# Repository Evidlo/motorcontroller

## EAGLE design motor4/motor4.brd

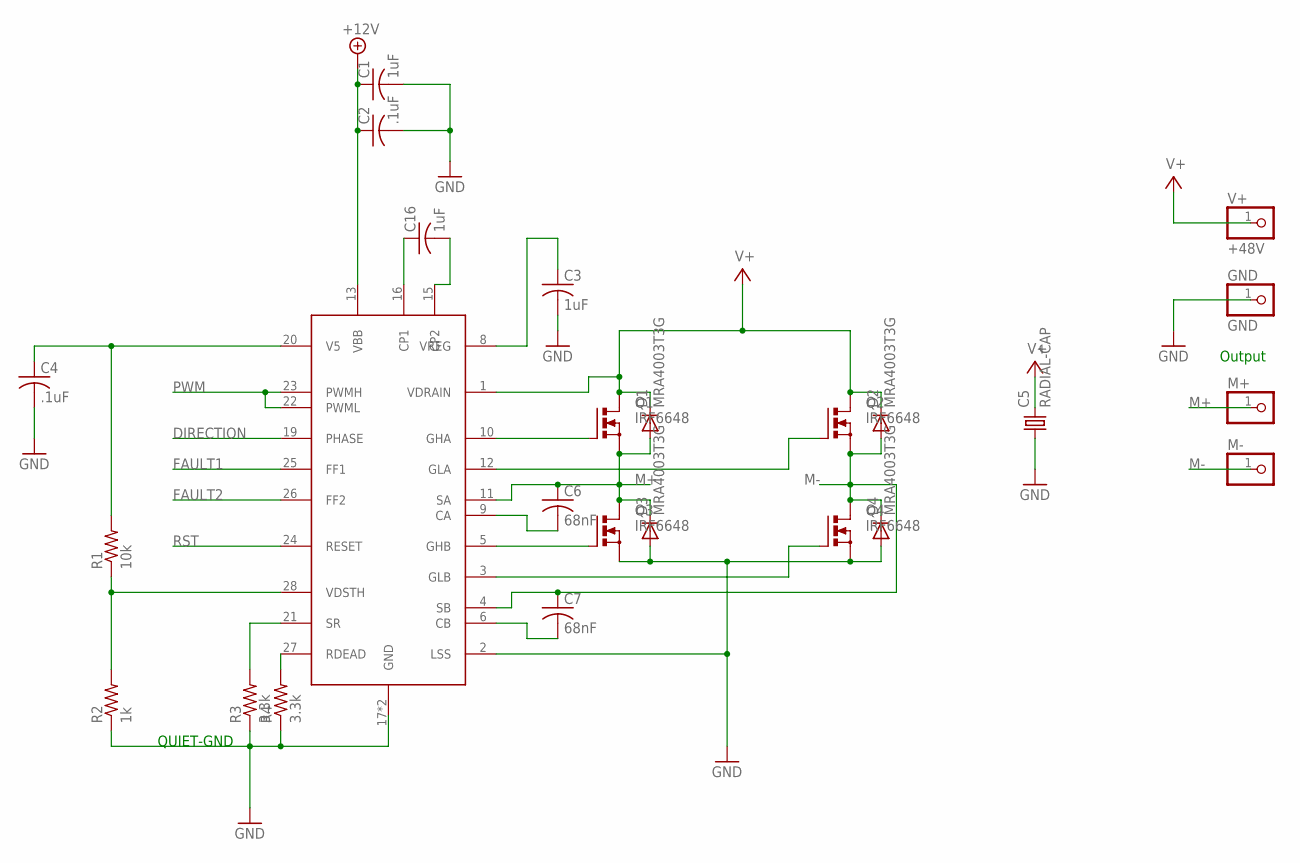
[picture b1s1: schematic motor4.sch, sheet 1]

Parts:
ALLGR: ALLEGRO-A3921; TSSOP28
C1, C3, C16: 1uF; C0603
C2, C4: .1uF; C0603
C5: RADIAL-CAP
C6, C7: 68nF; C0603
D1, D2, D3, D4: MRA4003T3G; SMA
GND: GND; 1X01
M+: PINHD-1X1; 1X01
M-: PINHD-1X1; 1X01
Q1, Q2, Q3, Q4: IRF6648; DIRECTFET
R1: 10k; R0603
R2: 1k; R0603
R3, R4: 3.3k; R0603
V+: +48V; 1X01

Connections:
+5V-A: ALLGR.20 (V5), C4.1, R1.2
+12V: ALLGR.13 (VBB), C1.1, C2.1; also elsewhere on the board
+48V: ALLGR.1 (VDRAIN), C5.P$1 (2), D1.C, D2.C, Q1.D@1 (D), Q1.D@2 (D), Q1.D@3 (D), Q1.D@4 (D), Q2.D@1 (D), Q2.D@2 (D), Q2.D@3 (D), Q2.D@4 (D), V+.1; also elsewhere on the board
DIRECTION: ALLGR.19 (PHASE); also elsewhere on the board
FAULT1: ALLGR.25 (FF1); also elsewhere on the board
FAULT2: ALLGR.26 (FF2); also elsewhere on the board
GND: ALLGR.2 (LSS), ALLGR.17 (GND), ALLGR.P$1 (GND), C1.2, C2.2, C3.2, C4.2, C5.P$2 (1), D3.A, D4.A, GND.1, Q3.S@1 (S), Q3.S@2 (S), Q4.S@1 (S), Q4.S@2 (S), R2.1, R3.1, R4.1; also elsewhere on the board
M+: ALLGR.11 (SA), C6.1, D1.A, D3.C, M+.1, Q1.S@1 (S), Q1.S@2 (S), Q3.D@1 (D), Q3.D@2 (D), Q3.D@3 (D), Q3.D@4 (D)
M-: ALLGR.4 (SB), C7.1, D2.A, D4.C, M-.1, Q2.S@1 (S), Q2.S@2 (S), Q4.D@1 (D), Q4.D@2 (D), Q4.D@3 (D), Q4.D@4 (D)
unnamed: ALLGR.8 (VREG), C3.1
unnamed: ALLGR.16 (CP1), C16.1
unnamed: ALLGR.15 (CP2), C16.2
unnamed: ALLGR.10 (GHA), Q1.G
unnamed: ALLGR.12 (GLA), Q2.G
unnamed: ALLGR.3 (GLB), Q4.G
unnamed: ALLGR.6 (CB), C7.2
unnamed: ALLGR.9 (CA), C6.2
unnamed: ALLGR.28 (VDSTH), R1.1, R2.2
unnamed: ALLGR.27 (RDEAD), R4.2
unnamed: ALLGR.5 (GHB), Q3.G
unnamed: ALLGR.21 (SR), R3.2
PWM: ALLGR.22 (PWML), ALLGR.23 (PWMH); also elsewhere on the board
RST: ALLGR.24 (RESET); also elsewhere on the board

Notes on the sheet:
QUIET-GND
Output

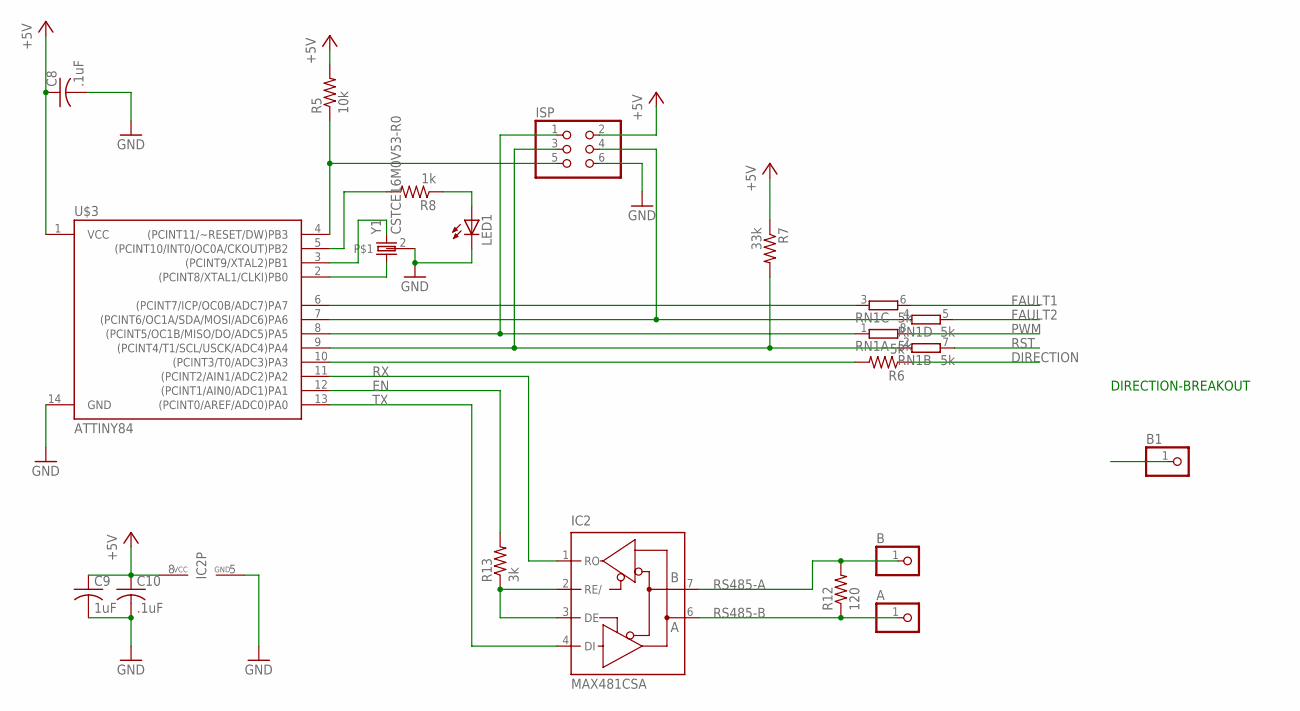
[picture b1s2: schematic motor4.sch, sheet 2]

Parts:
A: PINHD-1X1; 1X01
B, B1: PINHD-1X1; 1X01
C8, C10: .1uF; C0603
C9: 1uF; C0603
IC2: MAX481CSA; SO08
ISP: PINHD-2X3; 2X03
LED1: LEDCHIPLED_0603; CHIPLED_0603
R5: 10k; R0603
R6: 5k; R0603
R7: 33k; R0603
R8: 1k; R0603
R12: 120; R0603
R13: 3k; R0603
RN1: 5k; EXB38V
U$3: ATTINY84; SO14
Y1: CSTCE16M0V53-R0; MYSMD2_RESONATOR

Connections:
+5V: C8.1, C9.1, C10.1, IC2.8 (VCC), ISP.2, R5.2, R7.1, U$3.1 (VCC); also elsewhere on the board
DIRECTION: R6.1; also elsewhere on the board
EN: R13.2, U$3.12 ((PCINT1/AIN0/ADC1)PA1)
FAULT1: RN1.6 (2); also elsewhere on the board
FAULT2: RN1.5 (2); also elsewhere on the board
GND: C8.2, C9.2, C10.2, IC2.5 (GND), ISP.6, LED1.C, U$3.14 (GND), Y1.2; also elsewhere on the board
unnamed: ISP.1, RN1.1, U$3.8 ((PCINT5/OC1B/MISO/DO/ADC5)PA5)
unnamed: ISP.4, RN1.4 (1), U$3.7 ((PCINT6/OC1A/SDA/MOSI/ADC6)PA6)
unnamed: ISP.5, R5.1, U$3.4 ((PCINT11/~RESET/DW)PB3)
unnamed: IC2.2 (RE/), IC2.3 (DE), R13.1
unnamed: U$3.2 ((PCINT8/XTAL1/CLKI)PB0), Y1.1
unnamed: RN1.3 (1), U$3.6 ((PCINT7/ICP/OC0B/ADC7)PA7)
unnamed: B1.1, R6.2, U$3.10 ((PCINT3/T0/ADC3)PA3)
unnamed: U$3.3 ((PCINT9/XTAL2)PB1), Y1.3 (2)
unnamed: LED1.A, R8.1
unnamed: R8.2, U$3.5 ((PCINT10/INT0/OC0A/CKOUT)PB2)
OIJWOIJ3: ISP.3, R7.2, RN1.2 (1), U$3.9 ((PCINT4/T1/SCL/USCK/ADC4)PA4)
PWM: RN1.8 (2); also elsewhere on the board
RS485-A: B.1, IC2.7 (B), R12.2
RS485-B: A.1, IC2.6 (A), R12.1
RST: RN1.7 (2); also elsewhere on the board
RX: IC2.1 (RO), U$3.11 ((PCINT2/AIN1/ADC2)PA2)
TX: IC2.4 (DI), U$3.13 ((PCINT0/AREF/ADC0)PA0)

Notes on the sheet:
DIRECTION-BREAKOUT

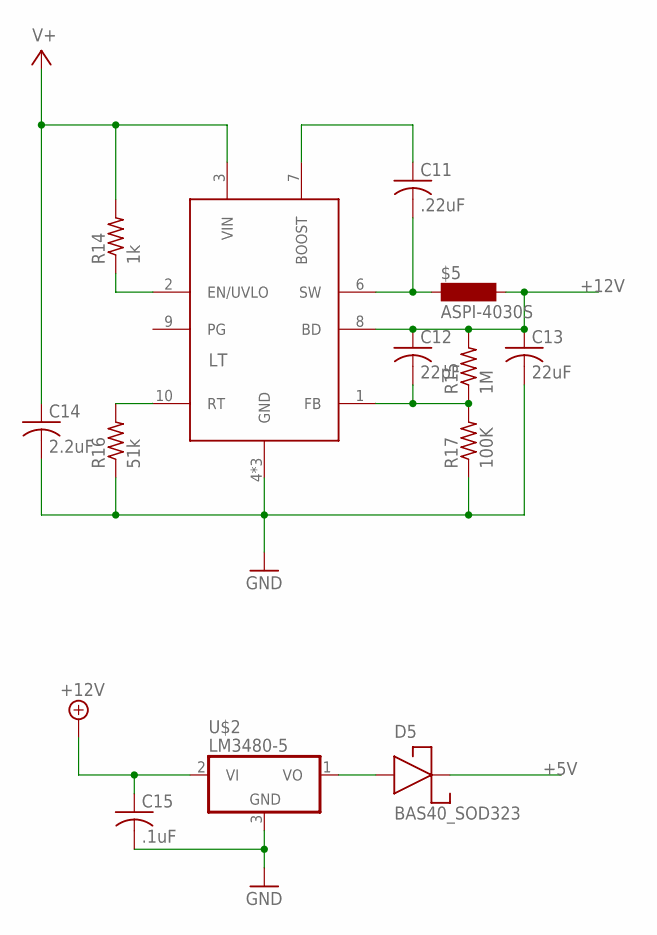
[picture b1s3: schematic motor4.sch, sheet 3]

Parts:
$5: ASPI-4030S
C11: .22uF; C0603
C12: 22pF; C0603
C13: 22uF; C0805
C14: 2.2uF; C0603
C15: .1uF; C0603
D5: BAS40_SOD323; SOD323
LT: LT3990; DFN10-3X3
R14: 1k; R0603
R15: 1M; R0603
R16: 51k; R0603
R17: 100K; R0603
U$2: LM3480-5; SOT23

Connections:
+5V: D5.1; also elsewhere on the board
+12V: $5.P$2 (2), C12.1, C13.1, C15.1, LT.8 (BD), R15.2, U$2.2 (VI); also elsewhere on the board
+48V: C14.1, LT.3 (VIN), R14.2; also elsewhere on the board
GND: C13.2, C14.2, C15.2, LT.4 (GND), LT.5 (GND), LT.EXP (GND), R16.1, R17.1, U$2.3 (GND); also elsewhere on the board
unnamed: C11.1, LT.7 (BOOST)
unnamed: $5.P$1 (1), C11.2, LT.6 (SW)
unnamed: C12.2, LT.1 (FB), R15.1, R17.2
unnamed: LT.10 (RT), R16.2
unnamed: D5.2, U$2.1 (VO)
unnamed: LT.2 (EN/UVLO), R14.1

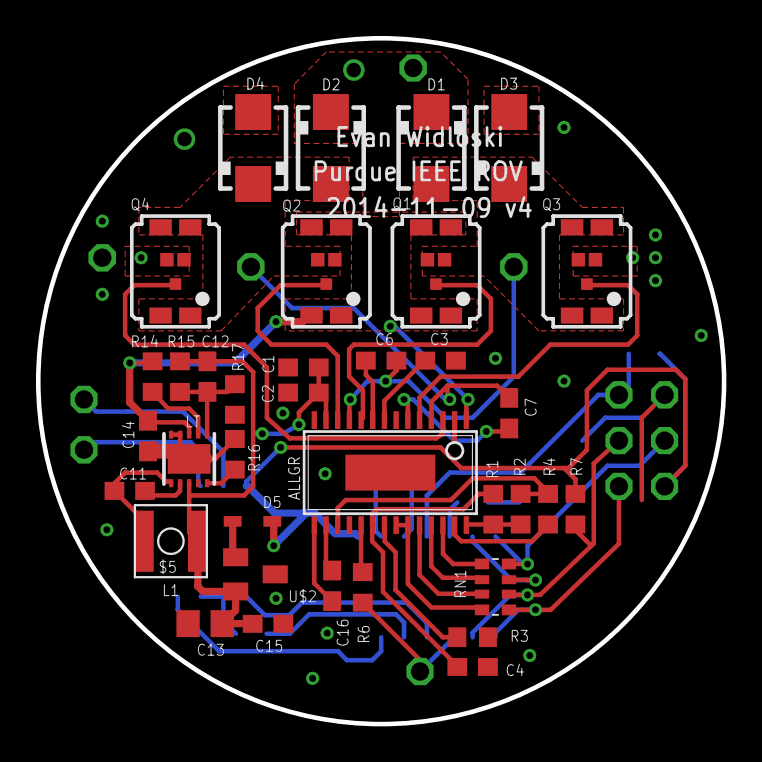
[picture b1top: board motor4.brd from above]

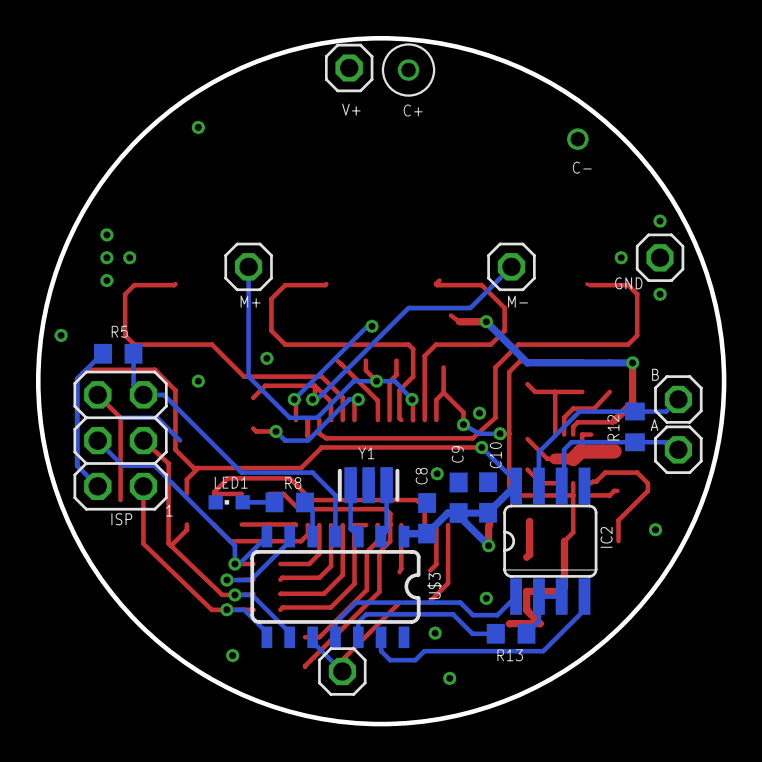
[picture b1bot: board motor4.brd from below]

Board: 2 copper layers, 38.1 x 38.1 mm, 56 parts (20 on the bottom side), 46 nets.

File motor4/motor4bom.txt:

Partlist exported from /home/evan/Dropbox/IEEE ROV 2015/electronics/boards/motor-controller/motor4/motor4.sch at 11/12/14 6:25 PM

Assembly variant: 

Part  Value           Device          Package          Description                                       
$5    ASPI-4030S      ASPI-4030S      ASPI-4030S                                                         
A                     PINHD-1X1       1X01             PIN HEADER                                        
ALLGR ALLEGRO-A3921   ALLEGRO-A3921   TSSOP28          Allegro A3921 Automotive Full Bridge Mosfet Driver
B                     PINHD-1X1       1X01             PIN HEADER                                        
B1                    PINHD-1X1       1X01             PIN HEADER                                        
C1    1uF             C-USC0603       C0603            CAPACITOR, American symbol                        
C2    .1uF            C-USC0603       C0603            CAPACITOR, American symbol                        
C3    1uF             C-USC0603       C0603            CAPACITOR, American symbol                        
C4    .1uF            C-USC0603       C0603            CAPACITOR, American symbol                        
C5    RADIAL-CAP      RADIAL-CAP      RADIAL-CAP                                                         
C6    68nF            C-USC0603       C0603            CAPACITOR, American symbol                        
C7    68nF            C-USC0603       C0603            CAPACITOR, American symbol                        
C8    .1uF            C-USC0603       C0603            CAPACITOR, American symbol                        
C9    1uF             C-USC0603       C0603            CAPACITOR, American symbol                        
C10   .1uF            C-USC0603       C0603            CAPACITOR, American symbol                        
C11   .22uF           C-USC0603       C0603            CAPACITOR, American symbol                        
C12   22pF            C-USC0603       C0603            CAPACITOR, American symbol                        
C12\  1uF             C-USC0603       C0603            CAPACITOR, American symbol                        
C13   22uF            C-USC0805       C0805            CAPACITOR, American symbol                        
C14   2.2uF           C-USC0603       C0603            CAPACITOR, American symbol                        
C15   .1uF            C-USC0603       C0603            CAPACITOR, American symbol                        
D1    MRA4003T3G      MRA4003T3G      SMA                                                                
D2    MRA4003T3G      MRA4003T3G      SMA                                                                
D3    MRA4003T3G      MRA4003T3G      SMA                                                                
D4    MRA4003T3G      MRA4003T3G      SMA                                                                
D5    BAS40_SOD323    BAS40_SOD323    SOD323                                                             
GND   GND             PINHD-1X1       1X01             PIN HEADER                                        
IC2   MAX481CSA       MAX481CSA       SO08             RS485 TRANSEIVER                                  
ISP                   PINHD-2X3       2X03             PIN HEADER                                        
LED1                  LEDCHIPLED_0603 CHIPLED_0603     LED                                               
LT    LT3990          LT3990          DFN10-3X3        http://cds.linear.com/docs/en/datasheet/3990fa.pdf
M+                    PINHD-1X1       1X01             PIN HEADER                                        
M-                    PINHD-1X1       1X01             PIN HEADER                                        
Q1    IRF6648         IRF6648         DIRECTFET        DirectFET Power MOSFET                            
Q2    IRF6648         IRF6648         DIRECTFET        DirectFET Power MOSFET                            
Q3    IRF6648         IRF6648         DIRECTFET        DirectFET Power MOSFET                            
Q4    IRF6648         IRF6648         DIRECTFET        DirectFET Power MOSFET                            
R1    10k             R-US_R0603      R0603            RESISTOR, American symbol                         
R2    1k              R-US_R0603      R0603            RESISTOR, American symbol                         
R3    3.3k            R-US_R0603      R0603            RESISTOR, American symbol                         
R4    3.3k            R-US_R0603      R0603            RESISTOR, American symbol                         
R5    10k             R-US_R0603      R0603            RESISTOR, American symbol                         
R6    5k              R-US_R0603      R0603            RESISTOR, American symbol                         
R7    33k             R-US_R0603      R0603            RESISTOR, American symbol                         
R8    1k              R-US_R0603      R0603            RESISTOR, American symbol                         
R12   120             R-US_R0603      R0603            RESISTOR, American symbol                         
R13   3k              R-US_R0603      R0603            RESISTOR, American symbol                         
R14   1k              R-US_R0603      R0603            RESISTOR, American symbol                         
R15   1M              R-US_R0603      R0603            RESISTOR, American symbol                         
R16   51k             R-US_R0603      R0603            RESISTOR, American symbol                         
R17   100K            R-US_R0603      R0603            RESISTOR, American symbol                         
RN1   5k              4R-NEXB38V      EXB38V           Array Chip Resistor                               
U$2   LM3480-5        LM3480-5        SOT23                                                              
U$3   ATTINY84        ATTINY84        SO14             Atmel 14-pin 2/4/8kB flash uC                     
V+    +48V            PINHD-1X1       1X01             PIN HEADER                                        
Y1    CSTCE16M0V53-R0 CSTCE16M0V53-R0 MYSMD2_RESONATOR

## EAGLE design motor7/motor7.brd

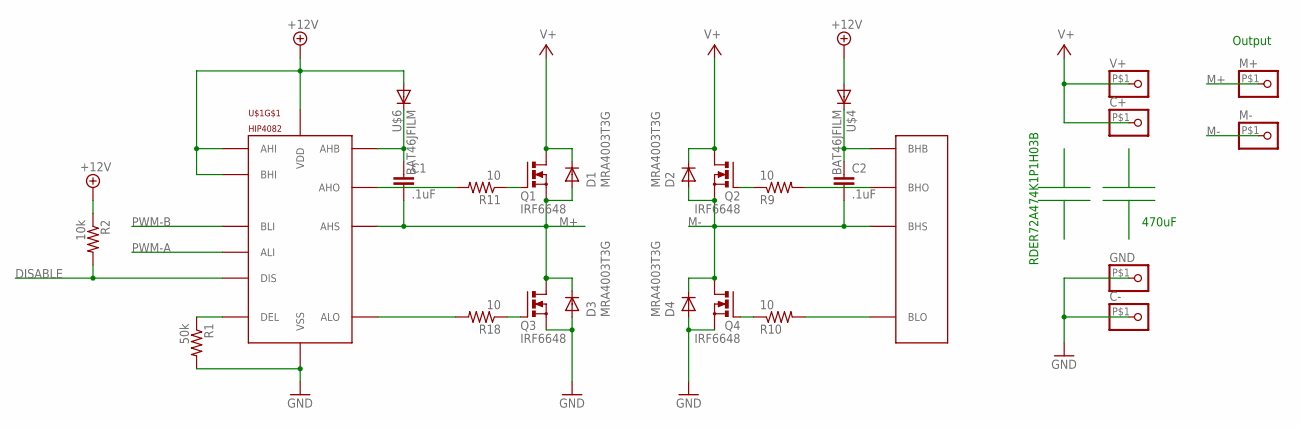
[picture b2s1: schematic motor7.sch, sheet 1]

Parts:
C1, C2: .1uF; C0603
C+: PINHD-1X1; 1X01
C-: PINHD-1X1; 1X01
D1, D2, D3, D4: MRA4003T3G; SMA
GND: PINHD-1X1; 1X01
M+: PINHD-1X1; 1X01
M-: PINHD-1X1; 1X01
Q1, Q2: IRF6648; DIRECTFET-MOD
Q3, Q4: IRF6648; DIRECTFET
R1: 50k; R0603
R2: 10k; R0603
R9, R10, R11, R18: 10; R0603
U$1: HIP4082; SOIC16
U$4, U$6: BAT46JFILM; SOD323
V+: PINHD-1X1; 1X01

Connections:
+12V: R2.1, U$1.2 (BHI), U$1.7 (AHI), U$1.12 (VDD), U$4.2 (A), U$6.2 (A); also elsewhere on the board
+48V: C+.P$1, D1.C, D2.C, Q1.D@1 (D), Q1.D@2 (D), Q1.D@3 (D), Q1.D@4 (D), Q2.D@1 (D), Q2.D@2 (D), Q2.D@3 (D), Q2.D@4 (D), V+.P$1; also elsewhere on the board
DISABLE: R2.2, U$1.8 (DIS); also elsewhere on the board
GND: C-.P$1, D3.A, D4.A, GND.P$1, Q3.S@1 (S), Q3.S@2 (S), Q4.S@1 (S), Q4.S@2 (S), R1.2, U$1.6 (VSS); also elsewhere on the board
M+: C1.2, D1.A, D3.C, M+.P$1, Q1.S@1 (S), Q1.S@2 (S), Q3.D@1 (D), Q3.D@2 (D), Q3.D@3 (D), Q3.D@4 (D), U$1.11 (AHS)
M-: C2.2, D2.A, D4.C, M-.P$1, Q2.S@1 (S), Q2.S@2 (S), Q4.D@1 (D), Q4.D@2 (D), Q4.D@3 (D), Q4.D@4 (D), U$1.15 (BHS)
unnamed: C1.1, U$1.9 (AHB), U$6.1 (C)
unnamed: R11.2, U$1.10 (AHO)
unnamed: R18.2, U$1.13 (ALO)
unnamed: C2.1, U$1.1 (BHB), U$4.1 (C)
unnamed: Q1.G, R11.1
unnamed: R10.2, U$1.14 (BLO)
unnamed: R9.2, U$1.16 (BHO)
unnamed: Q3.G, R18.1
unnamed: Q2.G, R9.1
unnamed: Q4.G, R10.1
unnamed: R1.1, U$1.5 (DEL)
PWM-A: U$1.4 (ALI); also elsewhere on the board
PWM-B: U$1.3 (BLI); also elsewhere on the board

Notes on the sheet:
Output
470uF
RDER72A474K1P1H03B

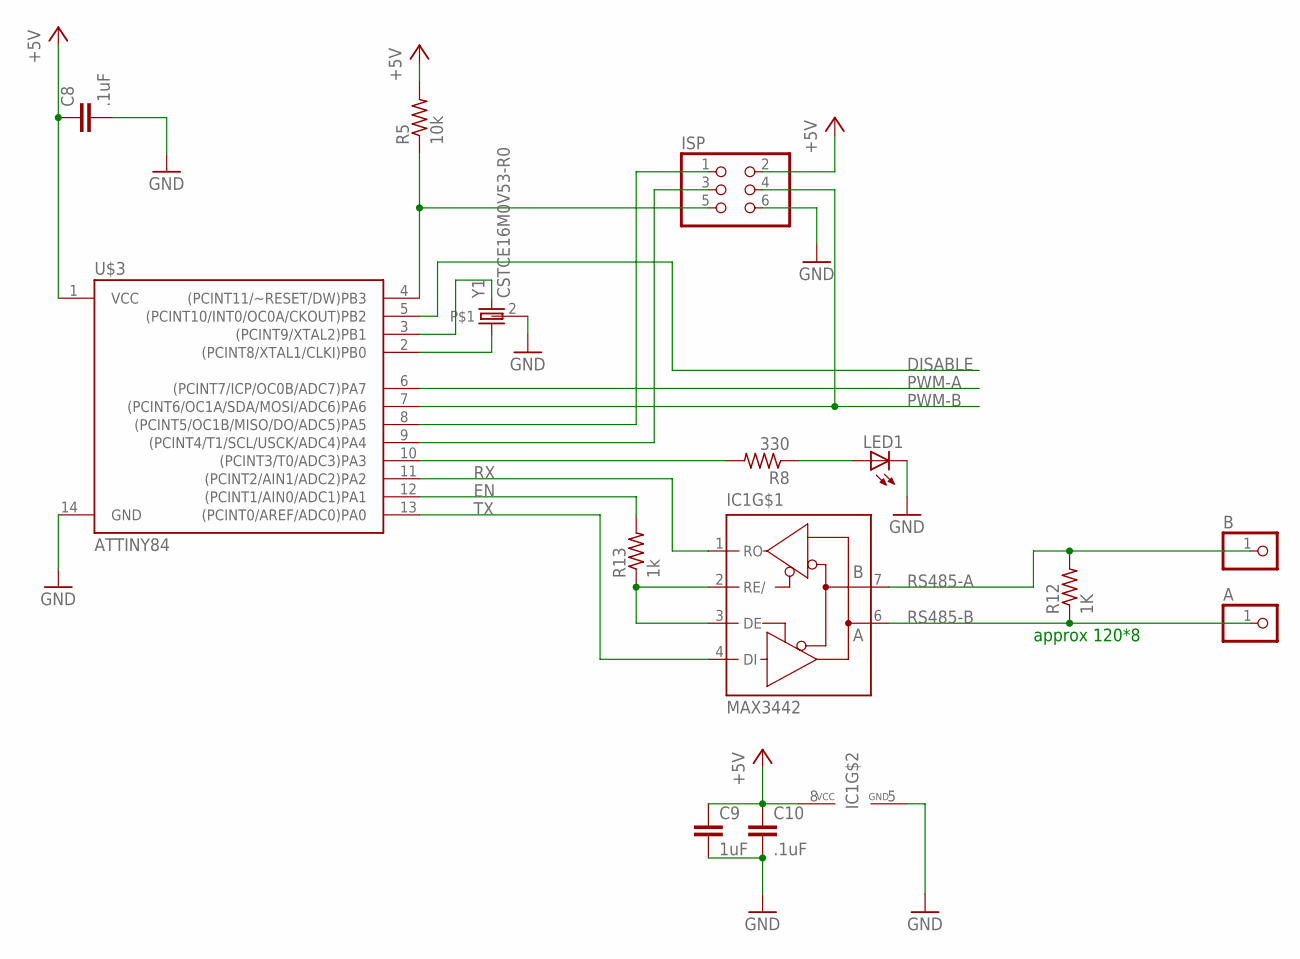
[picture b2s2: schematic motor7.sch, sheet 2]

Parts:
A: PINHD-1X1; 1X01
B: PINHD-1X1; 1X01
C8, C10: .1uF; C0603
C9: 1uF; C0603
IC1: MAX3442; SO08
ISP: PINHD-2X3; 2X03
LED1: LEDCHIPLED_0603; CHIPLED_0603
R5: 10k; R0603
R8: 330; R0603
R12: 1K; R0603
R13: 1k; R0603
U$3: ATTINY84; SO14
Y1: CSTCE16M0V53-R0; MYSMD2_RESONATOR

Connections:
23JOIJO: ISP.1, U$3.8 ((PCINT5/OC1B/MISO/DO/ADC5)PA5)
+5V: C8.1, C9.1, C10.1, IC1.8 (VCC), ISP.2, R5.2, U$3.1 (VCC); also elsewhere on the board
DISABLE: U$3.5 ((PCINT10/INT0/OC0A/CKOUT)PB2); also elsewhere on the board
EN: R13.2, U$3.12 ((PCINT1/AIN0/ADC1)PA1)
GND: C8.2, C9.2, C10.2, IC1.5 (GND), ISP.6, LED1.C, U$3.14 (GND), Y1.2; also elsewhere on the board
unnamed: IC1.2 (RE/), IC1.3 (DE), R13.1
unnamed: U$3.2 ((PCINT8/XTAL1/CLKI)PB0), Y1.1
unnamed: R8.2, U$3.10 ((PCINT3/T0/ADC3)PA3)
unnamed: U$3.3 ((PCINT9/XTAL2)PB1), Y1.3 (2)
unnamed: LED1.A, R8.1
unnamed: ISP.5, R5.1, U$3.4 ((PCINT11/~RESET/DW)PB3)
OIJWOIJ3: ISP.3, U$3.9 ((PCINT4/T1/SCL/USCK/ADC4)PA4)
PWM-A: U$3.6 ((PCINT7/ICP/OC0B/ADC7)PA7); also elsewhere on the board
PWM-B: ISP.4, U$3.7 ((PCINT6/OC1A/SDA/MOSI/ADC6)PA6); also elsewhere on the board
RS485-A: B.1, IC1.7 (B), R12.2
RS485-B: A.1, IC1.6 (A), R12.1
RX: IC1.1 (RO), U$3.11 ((PCINT2/AIN1/ADC2)PA2)
TX: IC1.4 (DI), U$3.13 ((PCINT0/AREF/ADC0)PA0)

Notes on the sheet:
approx 120*8

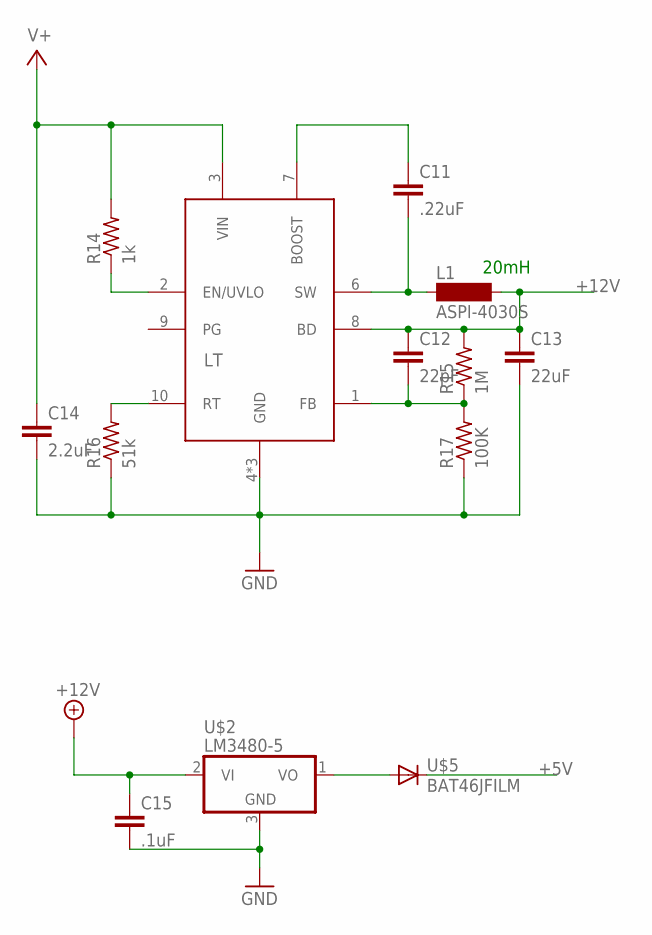
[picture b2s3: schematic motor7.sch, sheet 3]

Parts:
C11: .22uF; C0603
C12: 22pF; C0603
C13: 22uF; C0805
C14: 2.2uF; C0603
C15: .1uF; C0603
L1: ASPI-4030S
LT: LT3990; DFN10-3X3
R14: 1k; R0603
R15: 1M; R0603
R16: 51k; R0603
R17: 100K; R0603
U$2: LM3480-5; SOT23
U$5: BAT46JFILM; SOD323

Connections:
+5V: U$5.1 (C); also elsewhere on the board
+12V: C12.1, C13.1, C15.1, L1.P$2 (2), LT.8 (BD), R15.2, U$2.2 (VI); also elsewhere on the board
+48V: C14.1, LT.3 (VIN), R14.2; also elsewhere on the board
GND: C13.2, C14.2, C15.2, LT.4 (GND), LT.5 (GND), LT.EXP (GND), R16.1, R17.1, U$2.3 (GND); also elsewhere on the board
unnamed: C11.1, LT.7 (BOOST)
unnamed: C11.2, L1.P$1 (1), LT.6 (SW)
unnamed: C12.2, LT.1 (FB), R15.1, R17.2
unnamed: LT.10 (RT), R16.2
unnamed: U$2.1 (VO), U$5.2 (A)
unnamed: LT.2 (EN/UVLO), R14.1

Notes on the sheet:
20mH

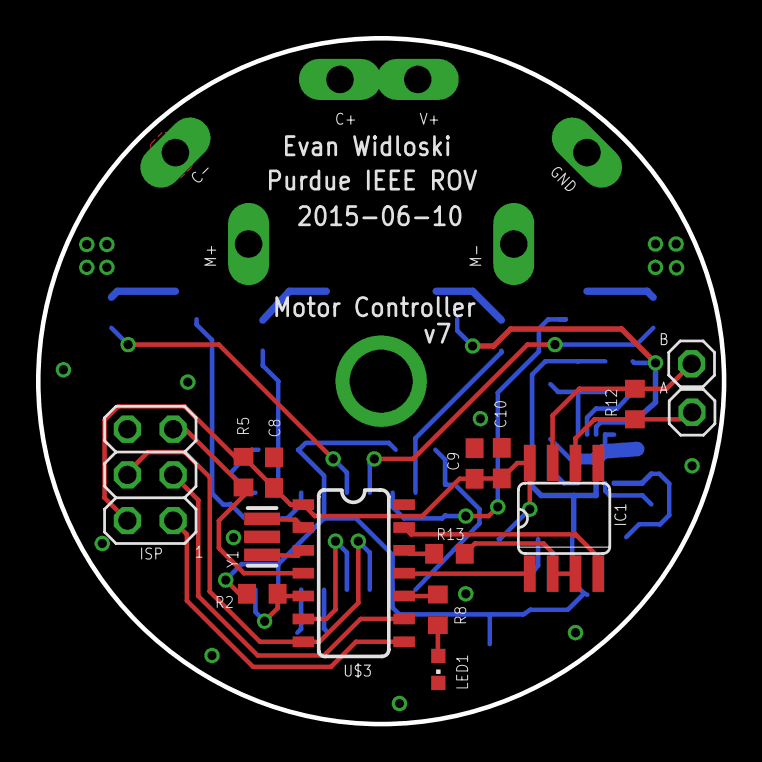
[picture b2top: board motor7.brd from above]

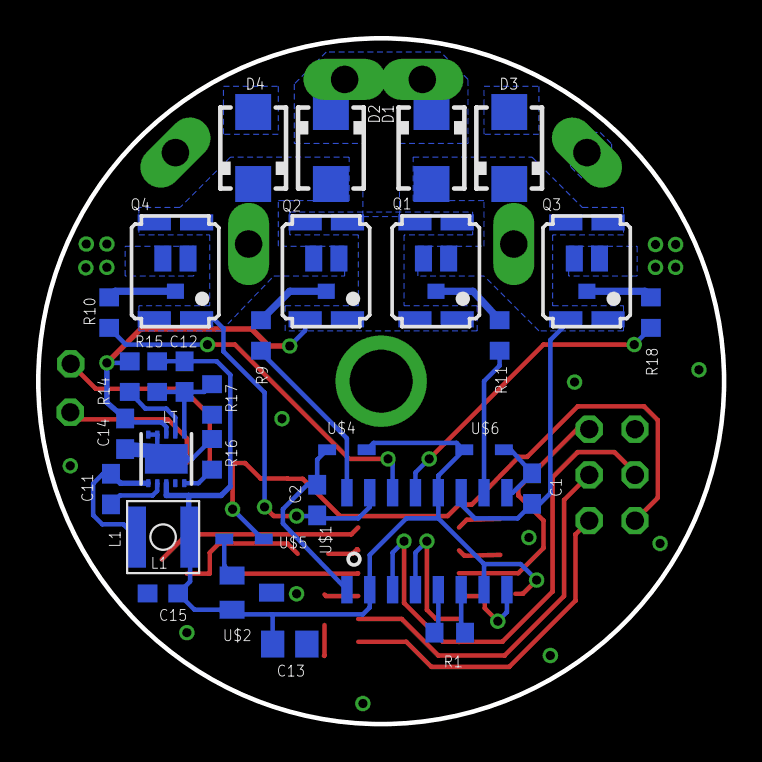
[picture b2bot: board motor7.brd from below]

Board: 2 copper layers, 38.1 x 38.1 mm, 52 parts (31 on the bottom side), 39 nets.

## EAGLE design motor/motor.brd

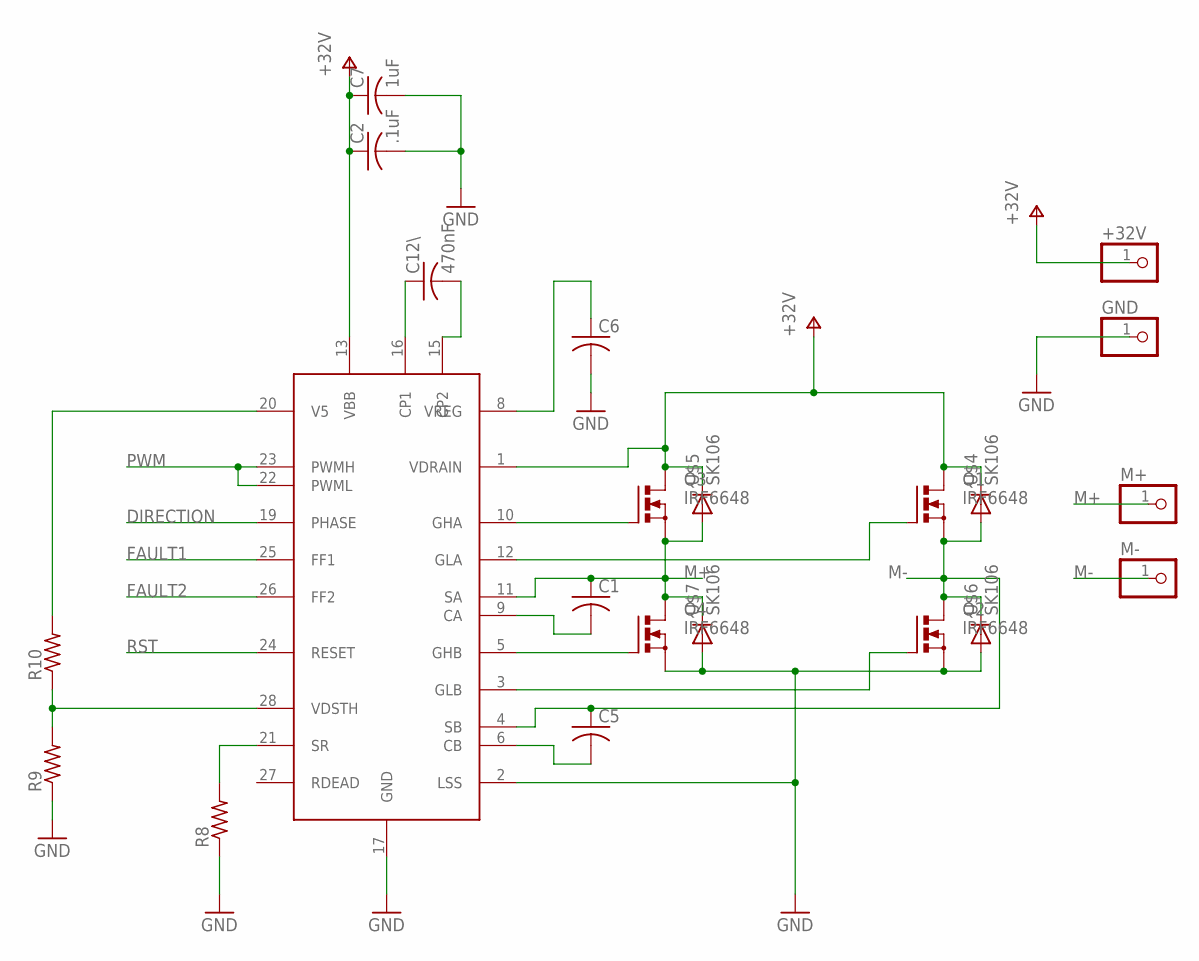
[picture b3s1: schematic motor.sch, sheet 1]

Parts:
+32V: PINHD-1X1; 1X01
C1, C5, C6: C-USC0603; C0603
C2: .1uF; C0603
C7: 1uF; C0603
C12\: 470nF; C0603
GND: PINHD-1X1; 1X01
M+: PINHD-1X1; 1X01
M-: PINHD-1X1; 1X01
Q1, Q2, Q3, Q4: IRF6648; DIRECTFET
R8, R9, R10: R-US_R0603; R0603
U$1: ALLEGRO-A3921; TSSOP28
U$4, U$5, U$6, U$7: SK106; DO-214AB

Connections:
+5V-A: R10.2, U$1.20 (V5)
+32V: +32V.1, C2.1, C7.1, Q1.D@1 (D), Q1.D@2 (D), Q1.D@3 (D), Q1.D@4 (D), Q3.D@1 (D), Q3.D@2 (D), Q3.D@3 (D), Q3.D@4 (D), U$1.1 (VDRAIN), U$1.13 (VBB), U$4.P$2 (C), U$5.P$2 (C); also elsewhere on the board
DIRECTION: U$1.19 (PHASE); also elsewhere on the board
FAULT1: U$1.25 (FF1); also elsewhere on the board
FAULT2: U$1.26 (FF2); also elsewhere on the board
GND: C2.2, C6.2, C7.2, GND.1, Q2.S@1 (S), Q2.S@2 (S), Q4.S@1 (S), Q4.S@2 (S), R8.1, R9.1, U$1.2 (LSS), U$1.17 (GND), U$6.P$1 (A), U$7.P$1 (A); also elsewhere on the board
M+: C1.1, M+.1, Q3.S@1 (S), Q3.S@2 (S), Q4.D@1 (D), Q4.D@2 (D), Q4.D@3 (D), Q4.D@4 (D), U$1.11 (SA), U$5.P$1 (A), U$7.P$2 (C)
M-: C5.1, M-.1, Q1.S@1 (S), Q1.S@2 (S), Q2.D@1 (D), Q2.D@2 (D), Q2.D@3 (D), Q2.D@4 (D), U$1.4 (SB), U$4.P$1 (A), U$6.P$2 (C)
unnamed: C6.1, U$1.8 (VREG)
unnamed: C12\.1, U$1.16 (CP1)
unnamed: C12\.2, U$1.15 (CP2)
unnamed: Q3.G, U$1.10 (GHA)
unnamed: Q1.G, U$1.12 (GLA)
unnamed: Q2.G, U$1.3 (GLB)
unnamed: C5.2, U$1.6 (CB)
unnamed: C1.2, U$1.9 (CA)
unnamed: R9.2, R10.1, U$1.28 (VDSTH)
unnamed: Q4.G, U$1.5 (GHB)
unnamed: R8.2, U$1.21 (SR)
PWM: U$1.22 (PWML), U$1.23 (PWMH); also elsewhere on the board
RST: U$1.24 (RESET); also elsewhere on the board

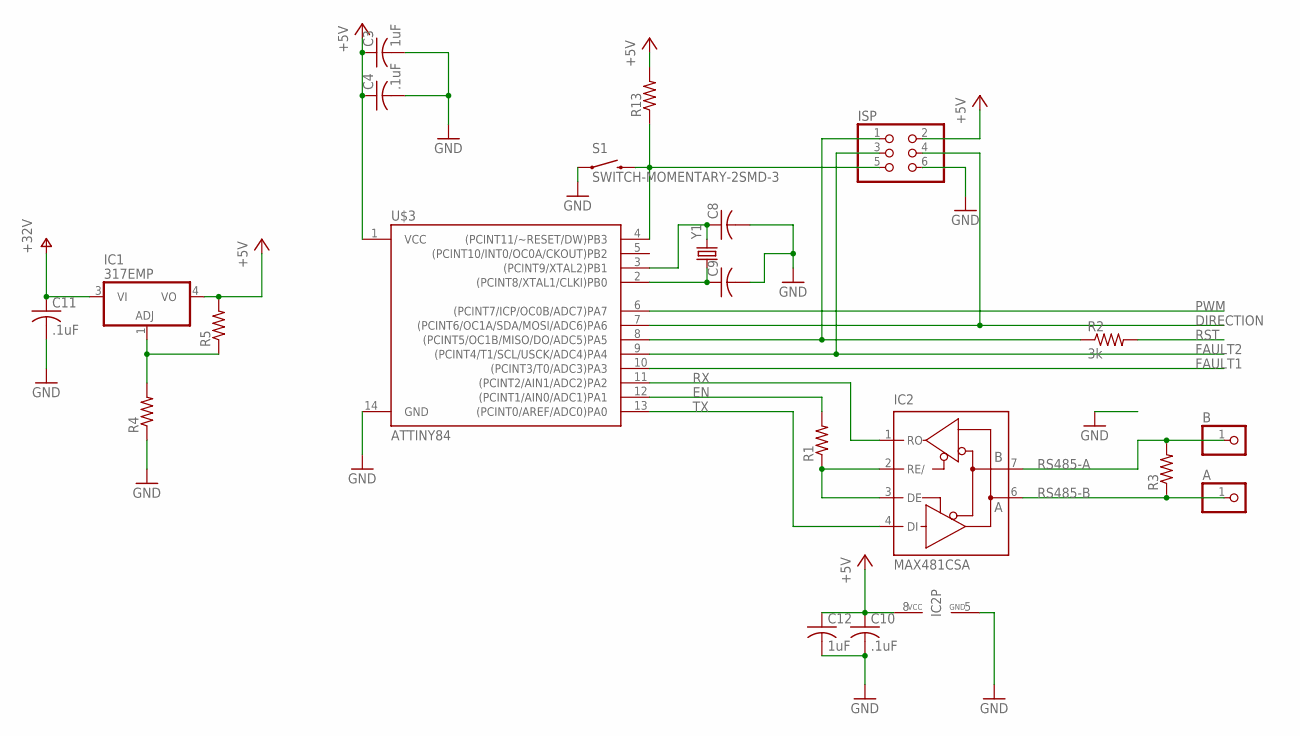
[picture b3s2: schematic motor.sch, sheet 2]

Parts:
A: PINHD-1X1; 1X01
B: PINHD-1X1; 1X01
C3, C12: 1uF; C0603
C4, C10, C11: .1uF; C0603
C8, C9: C-USC0603; C0603
IC1: 317EMP; SOT223
IC2: MAX481CSA; SO08
ISP: PINHD-2X3; 2X03
R1, R3, R4, R5, R13: R-US_R0603; R0603
R2: 3k; R0603
S1: SWITCH-MOMENTARY-2SMD-3; TACTILE_SWITCH_SMD-3
U$3: ATTINY84; SO14
Y1: CRYSTAL; MYSMD2_RESONATOR

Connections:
+5V: C3.1, C4.1, C10.1, C12.1, IC1.4 (VO), IC2.8 (VCC), ISP.2, R5.2, R13.2, U$3.1 (VCC)
+32V: C11.1, IC1.3 (VI); also elsewhere on the board
DIRECTION: ISP.4, U$3.7 ((PCINT6/OC1A/SDA/MOSI/ADC6)PA6); also elsewhere on the board
EN: R1.2, U$3.12 ((PCINT1/AIN0/ADC1)PA1)
FAULT1: U$3.10 ((PCINT3/T0/ADC3)PA3); also elsewhere on the board
FAULT2: ISP.3, U$3.9 ((PCINT4/T1/SCL/USCK/ADC4)PA4); also elsewhere on the board
GND: C3.2, C4.2, C8.2, C9.2, C10.2, C11.2, C12.2, IC2.5 (GND), ISP.6, R4.1, S1.1, U$3.14 (GND); also elsewhere on the board
unnamed: ISP.1, R2.1, U$3.8 ((PCINT5/OC1B/MISO/DO/ADC5)PA5)
unnamed: ISP.5, R13.1, S1.4 (2), U$3.4 ((PCINT11/~RESET/DW)PB3)
unnamed: IC2.2 (RE/), IC2.3 (DE), R1.1
unnamed: IC1.1 (ADJ), R4.2, R5.1
unnamed: C9.1, U$3.2 ((PCINT8/XTAL1/CLKI)PB0), Y1.1
unnamed: C8.1, U$3.3 ((PCINT9/XTAL2)PB1), Y1.3 (2)
PWM: U$3.6 ((PCINT7/ICP/OC0B/ADC7)PA7); also elsewhere on the board
RS485-A: B.1, IC2.7 (B), R3.2
RS485-B: A.1, IC2.6 (A), R3.1
RST: R2.2; also elsewhere on the board
RX: IC2.1 (RO), U$3.11 ((PCINT2/AIN1/ADC2)PA2)
TX: IC2.4 (DI), U$3.13 ((PCINT0/AREF/ADC0)PA0)

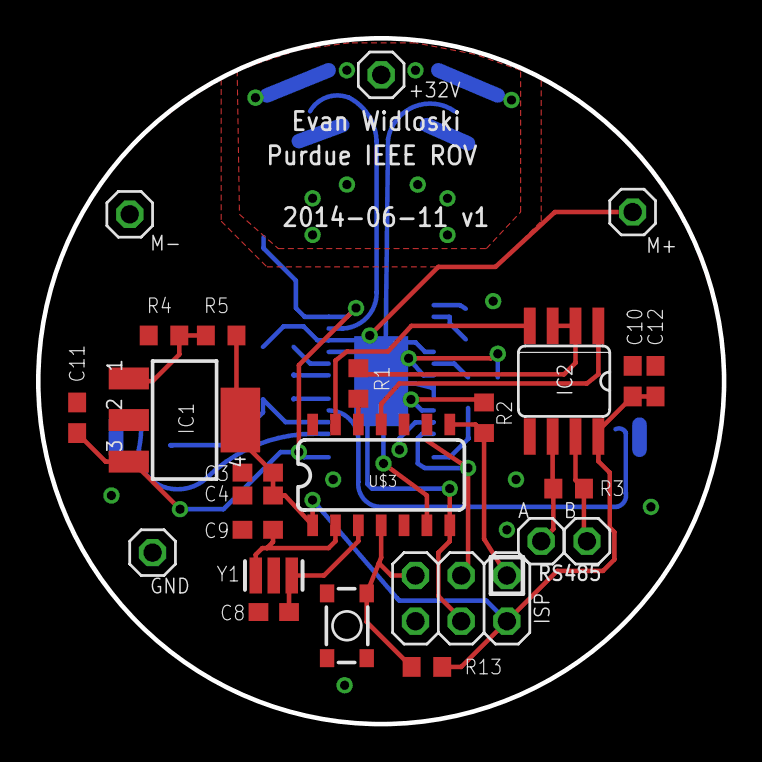
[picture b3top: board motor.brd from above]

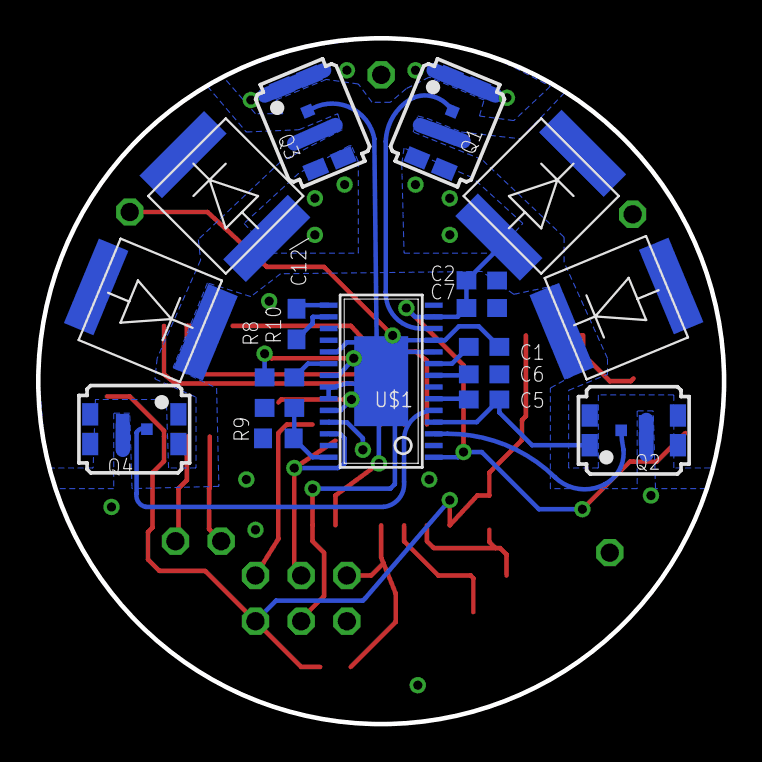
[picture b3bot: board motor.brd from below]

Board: 2 copper layers, 38.1 x 38.1 mm, 43 parts (18 on the bottom side), 33 nets.

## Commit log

2015-09-03 init commit

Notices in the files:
parts and their libraries:
SparkFun-Electromechanical: Licensing: CC v3.0 Share-Alike You are welcome to use this library for commercial purposes.
